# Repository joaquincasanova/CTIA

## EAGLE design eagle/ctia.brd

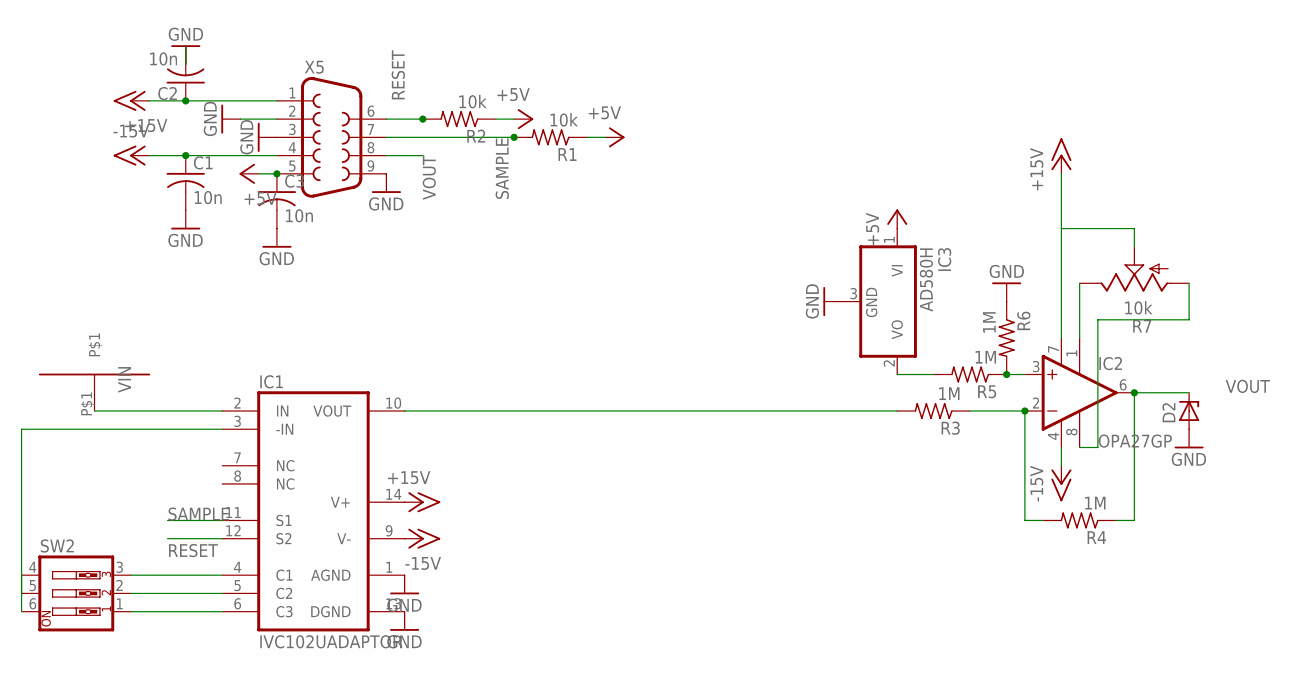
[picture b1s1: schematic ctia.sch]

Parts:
C1, C2, C3: 10n; C050-050X075
D2: ZENER-DIODEDO41Z10; DO41Z10
IC1: IVC102UADAPTOR; DIL14
IC2: OPA27GP; DIL08
IC3: AD580H; TO39
R1, R2: 10k; 0207/15
R3, R4, R5, R6: 1M; 0207/10
R7: 10k; B64Y
SW2: SW_DIP-3; EDG-03
U$1: CTIA
X5: F09HP

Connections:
+5V: C3.1, IC3.1 (VI), R1.1, R2.1, X5.5
+15V: C2.1, IC1.14 (V+), IC2.7 (V+), R7.S, X5.1
-15V: C1.1, IC1.9 (V-), IC2.4 (V-), X5.4
GND: C1.2, C2.2, C3.2, D2.A, IC1.1 (AGND), IC1.13 (DGND), IC3.3 (GND), R6.1, X5.2, X5.3, X5.9
unnamed: IC1.6 (C3), SW2.1
unnamed: IC1.5 (C2), SW2.2
unnamed: IC1.4 (C1), SW2.3
unnamed: IC1.3 (-IN), SW2.4, SW2.5, SW2.6
unnamed: IC1.10 (VOUT), R3.2
unnamed: IC2.2 (-IN), R3.1, R4.2
unnamed: IC2.3 (+IN), R5.1, R6.2
unnamed: IC3.2 (VO), R5.2
unnamed: IC2.1 (OFF1), R7.E
unnamed: IC2.8 (OFF2), R7.A
RESET: IC1.12 (S2), R2.2, X5.6
SAMPLE: IC1.11 (S1), R1.2, X5.7
VIN: IC1.2 (IN), U$1.P$1
VOUT: D2.C, IC2.6 (OUT), R4.1, X5.8

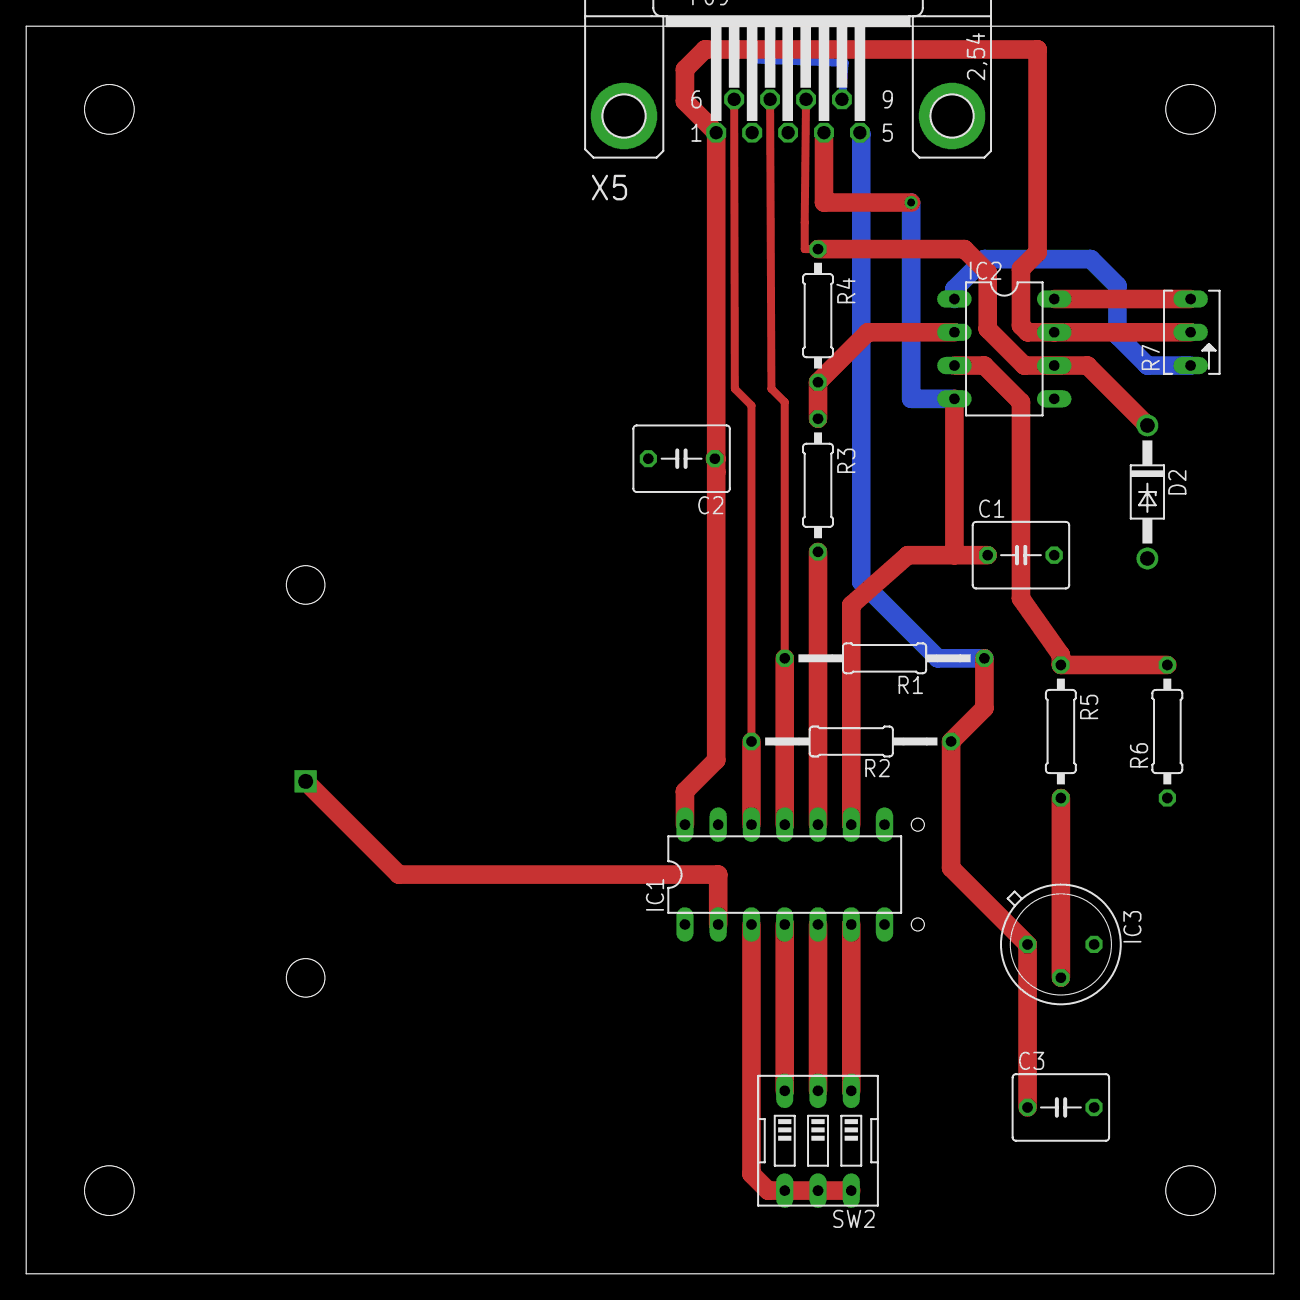
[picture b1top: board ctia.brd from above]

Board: 2 copper layers, 95.2 x 95.2 mm, 17 parts (1 on the bottom side), 18 nets.

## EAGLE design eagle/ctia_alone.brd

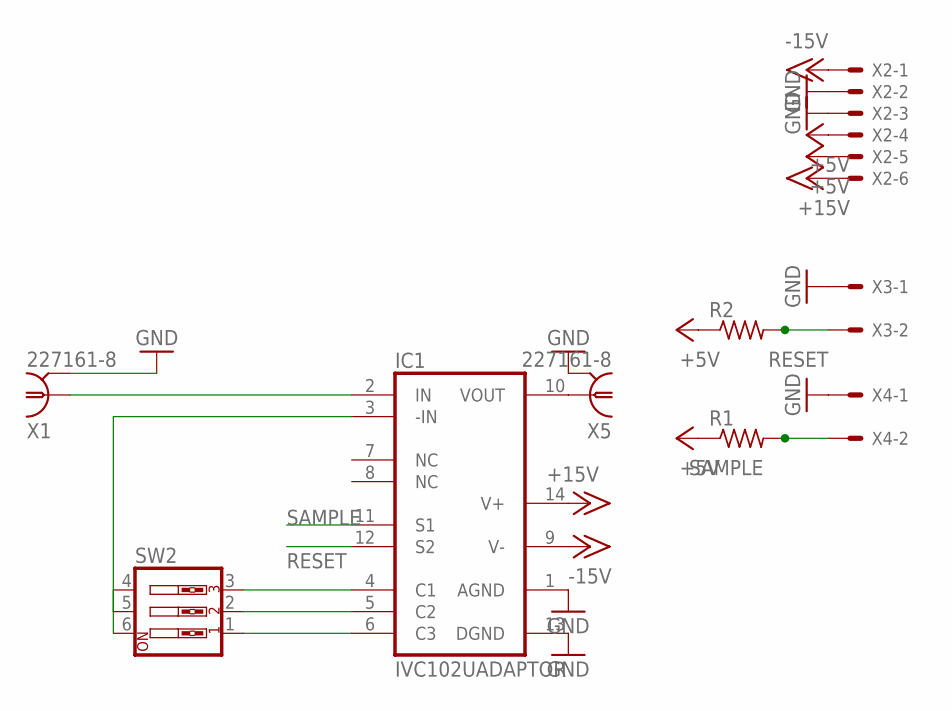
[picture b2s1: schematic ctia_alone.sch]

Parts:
IC1: IVC102UADAPTOR; DIL14
R1: R-US_0207/12; 0207/12
R2: R-US_0207/10; 0207/10
SW2: SW_DIP-3; EDG-03
X1, X5: 227161-8; AMP_227161
X2: KK-156-6
X3, X4: KK-156-2

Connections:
+5V: R1.1, R2.1, X2.4, X2.5
+15V: IC1.14 (V+), X2.6
-15V: IC1.9 (V-), X2.1
GND: IC1.1 (AGND), IC1.13 (DGND), X1.2, X2.2, X2.3, X3.1, X4.1, X5.2
unnamed: IC1.6 (C3), SW2.1
unnamed: IC1.5 (C2), SW2.2
unnamed: IC1.4 (C1), SW2.3
unnamed: IC1.3 (-IN), SW2.4, SW2.5, SW2.6
unnamed: IC1.2 (IN), X1.1
unnamed: IC1.10 (VOUT), X5.1
RESET: IC1.12 (S2), R2.2, X3.2
SAMPLE: IC1.11 (S1), R1.2, X4.2

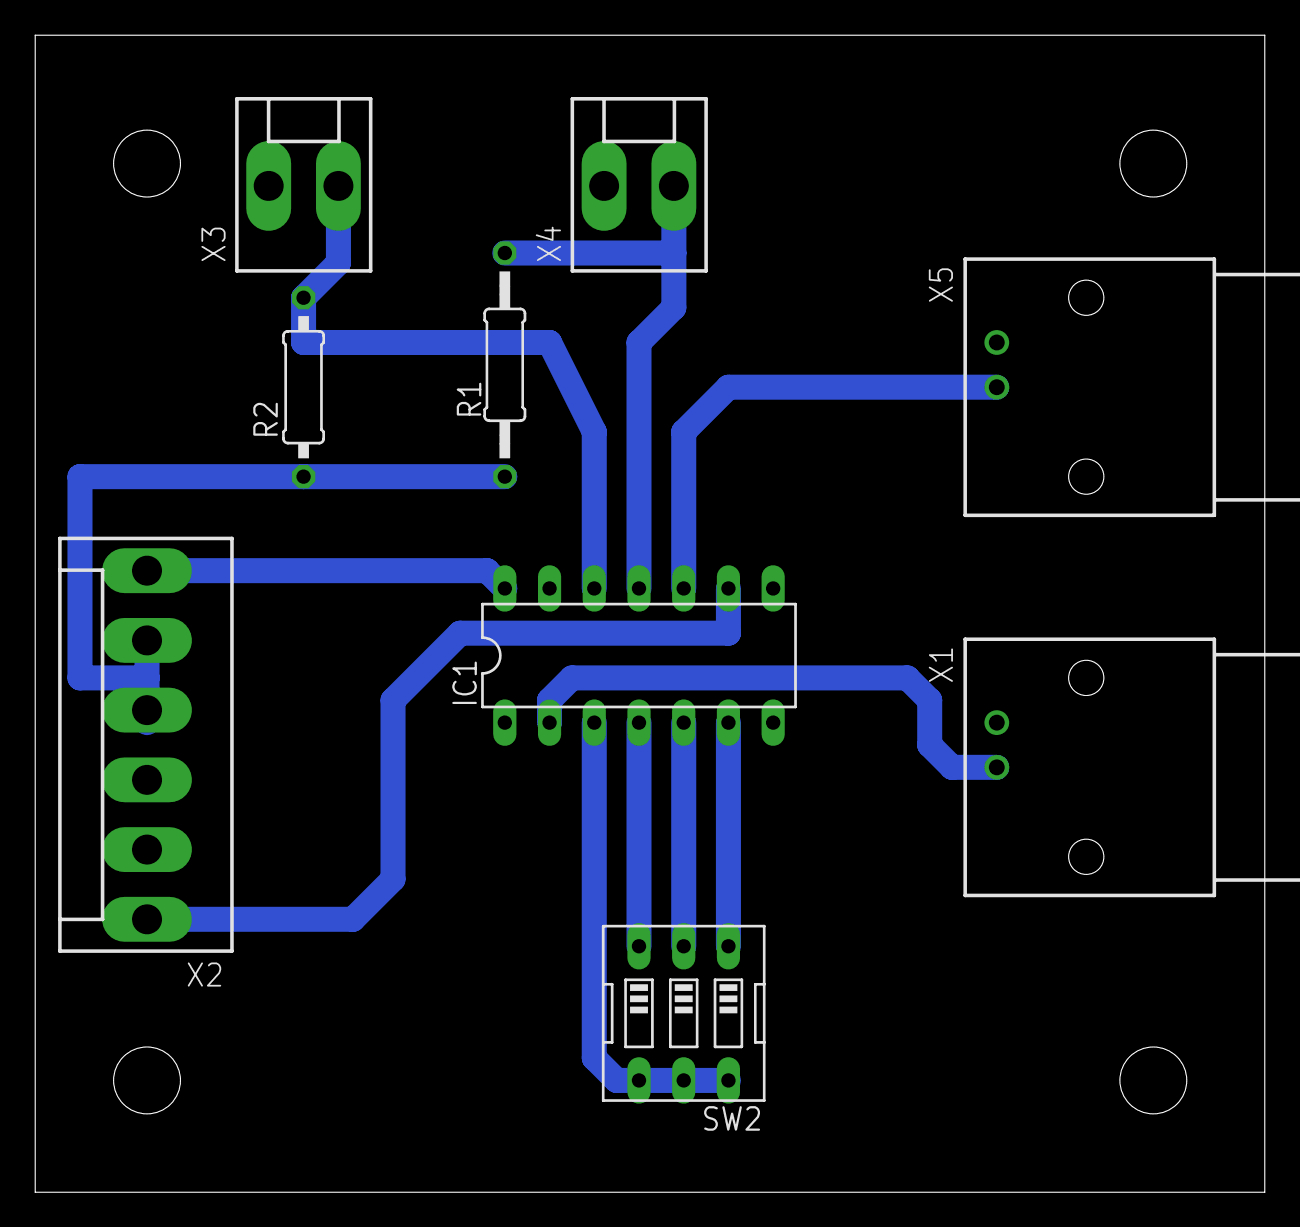
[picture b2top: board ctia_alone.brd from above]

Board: 2 copper layers, 69.8 x 65.7 mm, 9 parts (0 on the bottom side), 12 nets.

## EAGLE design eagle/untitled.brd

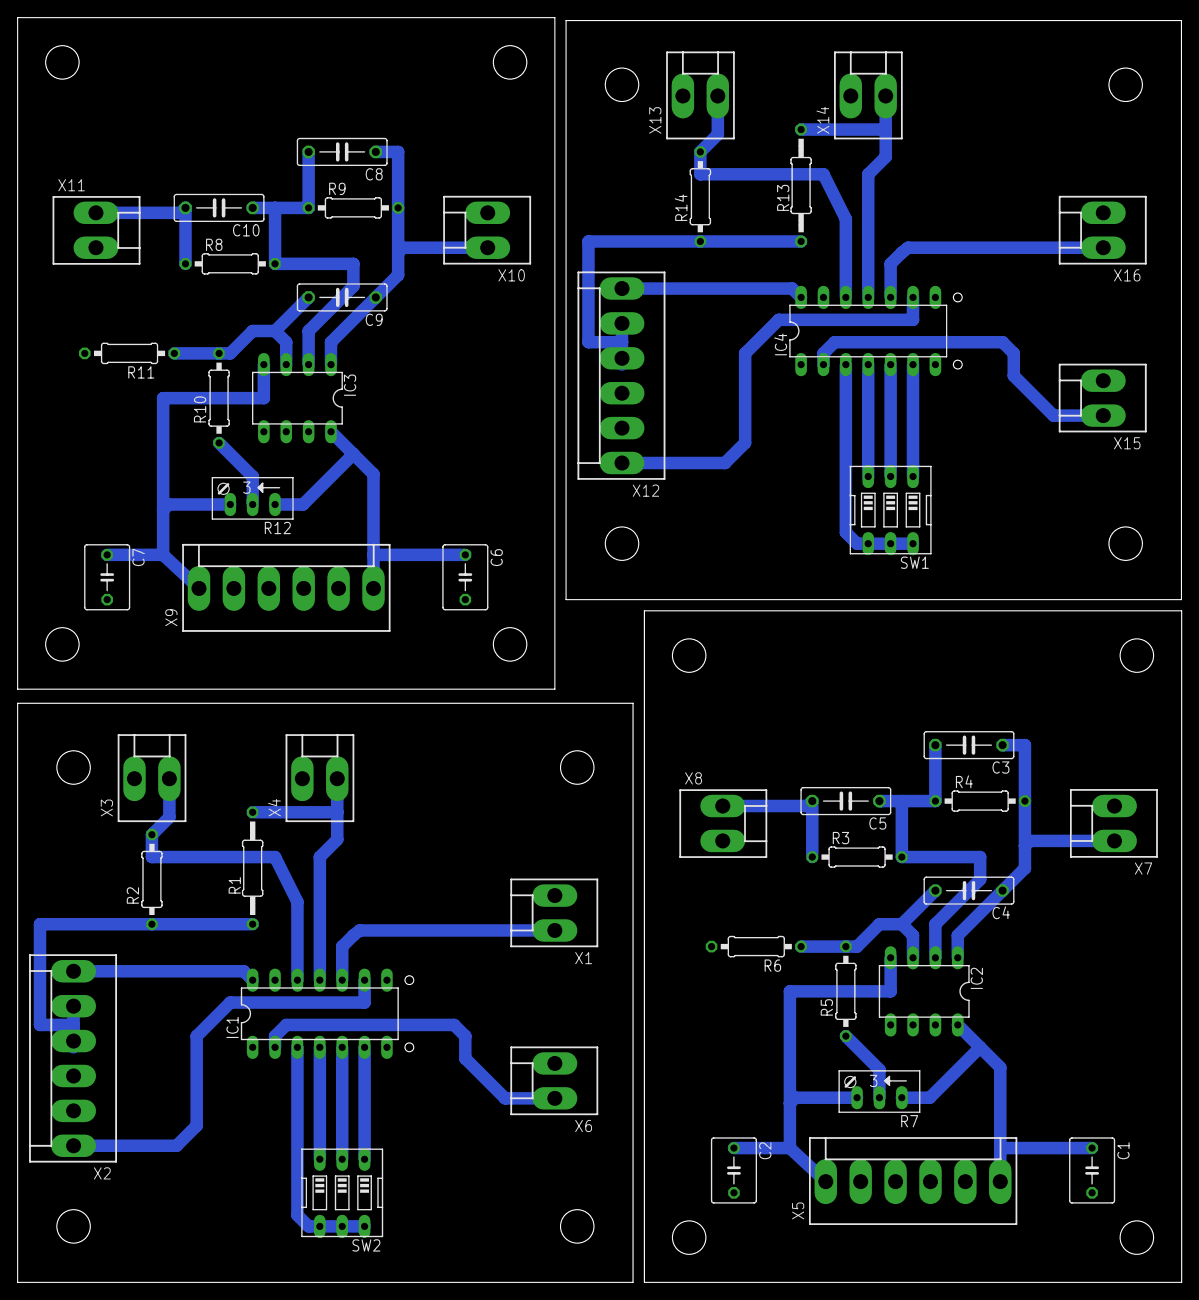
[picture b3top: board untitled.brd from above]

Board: 2 copper layers, 132.1 x 143.5 mm, 46 parts (0 on the bottom side), 42 nets.

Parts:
C1, C2, C6, C7: .1u; C050-050X075
C3, C8: gimmick; C075-032X103
C4, C9: 150p; C075-032X103
C5, C10: .68n; C075-032X103
IC1, IC4: IVC102UADAPTOR; DIL14
IC2, IC3: LF442N; DIL08
R1, R13: 0207/12
R2, R14: 0207/10
R3, R5, R8, R10: 1M; 0207/10
R4, R9: 10M; 0207/10
R6, R11: 649; 0207/10
R7, R12: 50k; RJ9W
SW1, SW2: EDG-03
X1, X3, X4, X6, X7, X8, X10, X11, X13, X14, X15, X16: KK-156-2
X2, X5, X9, X12: KK-156-6

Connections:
+5V: R1.1, R2.1, X2.4, X2.5
+5V1: X5.4, X5.5
+5V2: X9.4, X9.5
+5V3: R13.1, R14.1, X12.4, X12.5
+15V: IC1.14, X2.6
+15V1: C1.1, IC2.8, R7.E, X5.6
+15V2: C6.1, IC3.8, R12.E, X9.6
+15V3: IC4.14, X12.6
-15V: IC1.9, X2.1
-15V1: C2.1, IC2.4, R7.A, X5.1
-15V2: C7.1, IC3.4, R12.A, X9.1
-15V3: IC4.9, X12.1
GND: IC1.1, IC1.13, X1.2, X2.2, X2.3, X3.1, X4.1, X6.2
GND1: C1.2, C2.2, R6.2, X5.2, X5.3, X7.2, X8.2
GND2: C6.2, C7.2, R11.2, X9.2, X9.3, X10.2, X11.2
GND3: IC4.1, IC4.13, X12.2, X12.3, X13.1, X14.1, X15.2, X16.2
unnamed: IC1.6, SW2.1
unnamed: IC1.5, SW2.2
unnamed: IC1.4, SW2.3
unnamed: IC1.3, SW2.4, SW2.5, SW2.6
unnamed: IC1.2, X6.1
unnamed: IC1.10, X1.1
unnamed: C3.2, C5.1, IC2.2, R3.2, R4.1
unnamed: C3.1, C4.1, IC2.1, R4.2, X7.1
unnamed: C5.2, R3.1, X8.1
unnamed: C4.2, IC2.3, R5.2, R6.1
unnamed: R5.1, R7.S
unnamed: C8.2, C10.1, IC3.2, R8.2, R9.1
unnamed: C8.1, C9.1, IC3.1, R9.2, X10.1
unnamed: C10.2, R8.1, X11.1
unnamed: C9.2, IC3.3, R10.2, R11.1
unnamed: R10.1, R12.S
unnamed: IC4.6, SW1.1
unnamed: IC4.5, SW1.2
unnamed: IC4.4, SW1.3
unnamed: IC4.3, SW1.4, SW1.5, SW1.6
unnamed: IC4.2, X15.1
unnamed: IC4.10, X16.1
RESET: IC1.12, R2.2, X3.2
RESET1: IC4.12, R14.2, X13.2
SAMPLE: IC1.11, R1.2, X4.2
SAMPLE1: IC4.11, R13.2, X14.2

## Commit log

2016-01-29 :neckbeard: Added .gitattributes & .gitignore files
2016-01-29 first
2016-02-03 stand alone board for ctia test
2016-02-24 board/solid works
2016-02-24 flange & electrode solidworks
2016-02-29 flange alone board for test
2016-03-27 zener protect
2016-03-29 lower noise
